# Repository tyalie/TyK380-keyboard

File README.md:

# TyK380 - A Logitech K380 based custom membrane keyboard

This project uses Logitech K380 keyboard and fully replaces its internal logic,
equipping it with cool features like the ZMK keyboard firmware, USB and an integrated
Li-Ion battery.

## The "_Whyyy_ thoo?"

This project was born out of the need for a very robust but lightweight keyboard and
my custom key layout needs. I wanted a keyboard where one doesn't need an extra
casing when it is squeezed between your laptop and books inside an already struggling
backpack without losing the comfort of key layers, macros, tap-dance and more.

The choice fell on the Logitech K380, as it is easy to source, cheap (for a custom
keyboard), has a build in on/off switch and already very robust. Additional perks are
the membrane switches, which I personally prefer over normal MK switches and are
essentially indestructible.

## The mod

The actual logic inside the original K380 is contained on a small PCB in the upper
left corner (from the top) with the key matrix attached using an FPC cable. This
makes it really easy to trash it and put your own PCB inside. The Li-Ion battery also
fits snugly in the previous AAA battery compartment.

The `hardware` folder contains the schematic and PCB for the mod-chip. It uses an
nRF52840 processor for wireless (and wired) connectivity, uses WS2812 for status LEDs
and integrates a sensible Li-Ion charging IC. Except for the newly added USB port and
a few more LED colors, the mod is essentially indistinguishable from the outside.

The only part of the mod, that requires a bit more effort besides potentially
soldering the PCB, is the drilling on the case for the USB-C port. In my first
revisions also integrated a completely oversized Li-Ion battery which didn't fit into
the battery bay without some subtractive manufacturing.

### Features

- nRF52840 - a low power, but feature-rich wireless IC
- ZMK support
- easy to integrate
- replaces AAA batteries with a Li-Ion battery
- a fully functioning USB port, for charging, connecting and programming
- RGB status LEDs

### Limitations

Besides not being able to really mix up the keyboard layout, the biggest problem
there is with the keyboard is the lack of phantom key blocking. The keyboard matrix
itself lacks any kind of diodes - presumably to save on costs - and is such prone to
ghosting. In normal use one doesn't really notice that, as the vendor firmware only
supports three key presses at a time and the key matrix traces are routed all over
the place, so that common key combinations won't result in ghost key presses.

## Contributing

Before you start editing the hardware here, you should install the [marbastlib
plugin](https://github.com/ebastler/marbastlib) into your KiCad. It contains the
footprints and 3D models for the HolyIoT board.

Otherwise, feel free to go. But if you want to contribute anything to the main
hardware, please open an issue first. I'm currently a bit unsure how collaboration
could work with KiCad projects as merging changes isn't really trivial here.

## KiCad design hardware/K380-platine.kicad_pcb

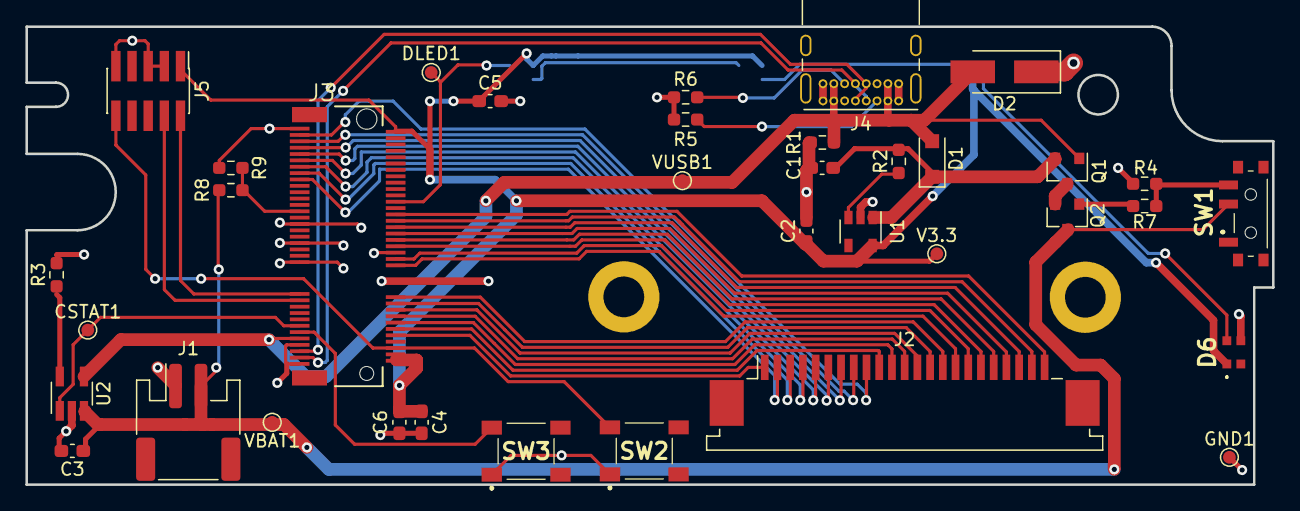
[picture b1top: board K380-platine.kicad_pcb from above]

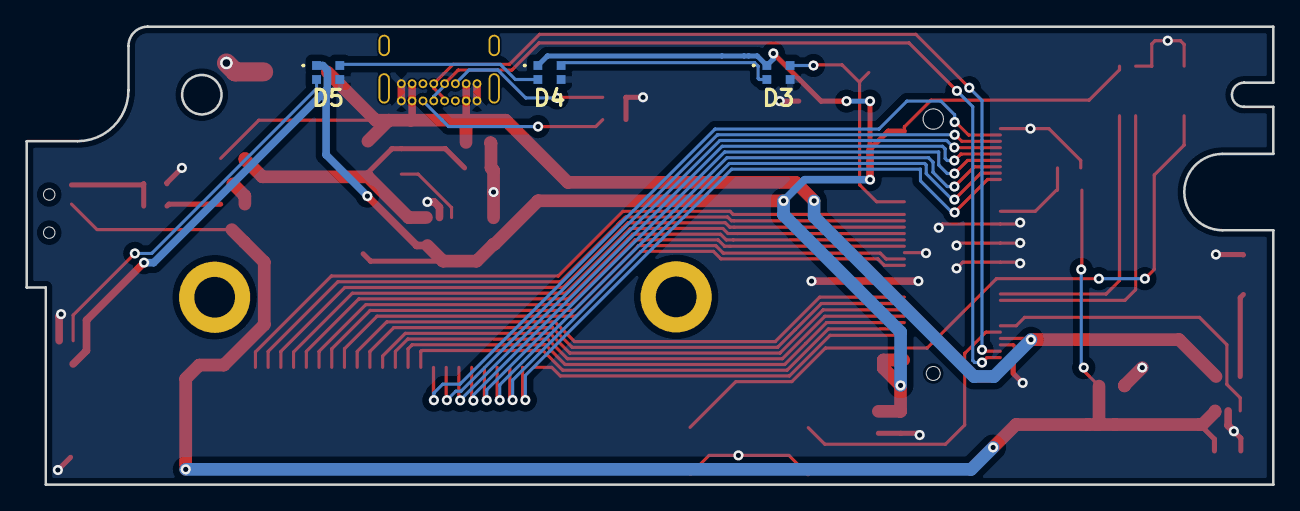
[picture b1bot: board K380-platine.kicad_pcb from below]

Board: 2 copper layers, 98.0 x 36.0 mm, 39 parts (3 on the bottom side), 48 nets.

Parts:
C1, C3, C4: 10uF; C_0603_1608Metric_Pad1.08x0.95mm_HandSolder
C2: 4.7uF; C_0603_1608Metric_Pad1.08x0.95mm_HandSolder
C5, C6: 0.1uF; C_0603_1608Metric_Pad1.08x0.95mm_HandSolder
CSTAT1: T_CSTAT; TestPoint_Pad_D1.0mm
D1: MBR1020VL; D_SOD-123F
D2: TVS 5V; D_SMA_Handsoldering
D3, D4, D5, D6: WS2812B; WS28122020
DLED1: T_DLED; TestPoint_Pad_D1.0mm
GND1: T_GND; TestPoint_Pad_D1.0mm
J1: JST-PH 2; JST_PH_S2B-PH-SM4-TB_1x02-1MP_P2.00mm_Horizontal
J2: Conn_01x23; TE_2-84952-3_1x23-1MP_P1.0mm_Horizontal
J3: MicroMod-M.2E; M.2-CONNECTOR-E
J4: USB_C_Receptacle_USB2.0; USB_C_Receptacle_GCT_USB4085
J5: Conn_ARM_JTAG_SWD_10; PinHeader_2x05_P1.27mm_Vertical_SMD
Q1: PMost Enc FET -20V; SOT-23
Q2: Q_NMOS_DGS; SOT-23
R1, R2, R8, R9: 100K; R_0603_1608Metric_Pad0.98x0.95mm_HandSolder
R3: RProg; R_0603_1608Metric_Pad0.98x0.95mm_HandSolder
R4: 100M; R_0603_1608Metric_Pad0.98x0.95mm_HandSolder
R5, R6: 5.1k 20%; R_0603_1608Metric_Pad0.98x0.95mm_HandSolder
R7: 100; R_0603_1608Metric_Pad0.98x0.95mm_HandSolder
SW1: EG1215AA
SW2, SW3: SW_Push; MJTP1140AAUTR - Fixed
U1: XC6220B331MR; SOT-23-5
U2: MCP73831-2-OT; SOT-23-5_HandSoldering
V3.3: T_V3.3; TestPoint_Pad_D1.0mm
VBAT1: T_VBAT; TestPoint_Pad_D1.0mm
VUSB1: T_VUSB; TestPoint_Pad_D1.0mm

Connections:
+3V3: C2.1, C4.1, C5.1, C6.1, D3.4 (VDD), D4.4 (VDD), D5.4 (VDD), D6.4 (VDD), J3.2 (3.3V), J3.4 (3.3V), J3.74 (3.3V), J5.1 (VTref), U1.5 (VOUT), V3.3.1
+BATT: C3.1, J1.2, Q2.3 (D), R8.1, SW1.2 (B), U2.3 (VBAT)
/SWO: J3.70 (SPI_~CS1(P1.00)), J5.6 (SWO/TDO)
BOOT: J3.11 (~BOOT), SW3.2
COL1: J2.1, J3.10 (P0.27)
COL2: J2.10, J3.12 (P0.08)
COL3: J2.11, J3.14 (P0.11)
COL4: J2.12, J3.16 (P0.15)
COL5: J2.13, J3.18 (P1.08)
COL6: J2.14, J3.20 (P1.05)
COL7: J2.15, J3.22 (P1.07)
COL8: J2.16, J3.32 (P0.06)
COL9: J2.17, J3.34 (P0.04(AIN2))
COL10: J2.18, J3.38 (P0.05(AIN3))
COL11: J2.19, J3.40 (P0.29(AIN5))
COL12: J2.20, J3.42 (P0.03(AIN1))
COL13: J2.21, J3.44 (P1.13)
COL14: J2.22, J3.46 (P1.12)
COL15: J2.23, J3.48 (P1.11)
CSTAT: CSTAT1.1, J3.13 (P1.02), U2.1 (STAT)
D+: J3.3 (USB_D+), J4.A6 (D+), J4.B6 (D+)
D-: J3.5 (USB_D-), J4.A7 (D-), J4.B7 (D-)
DLED: D3.3 (DIN), DLED1.1, J3.52 (P0.26)
GND: C1.2, C2.2, C3.2, C4.2, C5.2, C6.2, D2.1 (A1), D3.2 (VSS), D4.2 (VSS), D5.2 (VSS), D6.2 (VSS), GND1.1, J1.1, J3.1 (GND), J3.7 (GND), J3.33 (GND), J3.36 (GND), J3.39 (GND), J3.45 (GND), J3.75 (GND), J4.A1 (GND), J4.A12 (GND), J4.B1 (GND), J4.B12 (GND), J5.3 (GND), J5.5 (GND), J5.9 (GNDDetect), R1.2, R3.2, R4.2, R5.1, R6.1, R9.2, SW2.1, SW3.1, U1.2 (GND), U2.2 (VSS)
unnamed: C1.1, D1.1 (K), Q1.2 (S), R2.2, U1.1 (VIN)
unnamed: D3.1 (DOUT), D4.3 (DIN)
unnamed: D4.1 (DOUT), D5.3 (DIN)
unnamed: D5.1 (DOUT), D6.3 (DIN)
unnamed: J4.A5 (CC1), R5.2
unnamed: J4.B5 (CC2), R6.2
unnamed: Q1.3 (D), Q2.2 (S)
unnamed: Q2.1 (G), R7.1
unnamed: R4.1, R7.2, SW1.3 (C)
unnamed: R2.1, U1.3 (CE)
unnamed: R3.1, U2.5 (PROG)
RESET: J3.6 (~RESET), J5.10 (~RESET), SW2.2
ROW1: J2.2, J3.59 (P0.31(AIN7))
ROW2: J2.3, J3.61 (P0.02(AIN0))
ROW3: J2.4, J3.63 (P0.10)
ROW4: J2.5, J3.65 (P0.09)
ROW5: J2.6, J3.67 (P1.14)
ROW6: J2.7, J3.69 (P1.04)
ROW7: J2.8, J3.71 (P1.06)
ROW8: J2.9, J3.73 (P0.17)
SWDCLK: J3.21 (SWDCK), J5.4 (SWDCLK/TCK)
SWDIO: J3.23 (SWDIO), J5.2 (SWDIO/TMS)
VBUS: D1.2 (A), D2.2 (A2), J3.9 (USB_VIN), J4.A4 (VBUS), J4.A9 (VBUS), J4.B4 (VBUS), J4.B9 (VBUS), Q1.1 (G), R1.1, U2.4 (VDD), VUSB1.1
VDIV: J3.49 (P0.30(AIN6)), R8.2, R9.1

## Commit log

2022-05-26 Basic PCB outline of K380 keyboard
2022-05-26 Add few major components
    - completely unconnected
    - created schematic for M.2 sparkfun nRF52840 module
    - included SparkFun footprint library
    - position a few major components on the footprint
2022-05-27 Schem: Add Power and Charging Circuit
2022-05-28 Wired USB-C
2022-05-29 Add battery con and user switches
    - changed schematic page design
    - battery can be disabled via slider switch
    - integrated library loader
    - add user and reset switch
2022-05-29 Add status LEDs
2022-05-29 Finish schematics
    - decoupling capacitors
    - connected keyboard matrix
    - changed from user to boot pin
    - add SWD connector
    - connect MicroMod connector
2022-05-29 Assigned footprint to all components
2022-05-29 Fix footprint of USB-c connector
2022-05-29 Basic sorting of components on footprint
2022-05-29 Reordered keyboard matrix pins
    - layout traces isn't as random as before
2022-05-29 Finished basic layout
2022-05-29 Change pin of DLED and CSTAT
    - cstat was misspelled so KiCad made no connection
    - DLED is closer to where it needs to be
2022-05-29 Small layout changes to improve routing
2022-05-29 Finished routing
    - GND is zone fill in bottom
2022-05-30 Simplified tracks
    as GND got to be the bottom layer, a few tracks were able be routed
    differently, simplifying the layout and increasing the connection
    between larger sections of GND.
    Also on a few components connection to GND was given the same track
    width as the power delivering lines connected to them.
2022-05-30 Add drill mills
    - needed to reroute a few tracks for it to fit
2022-05-30 Add test probes
2022-05-30 Removed unnecessary text on silk screen
    Drill holes had Ref** on PCB
2022-05-30 Moved a few silk screen text that were unreadable
2022-07-02 Add debug-keymatrix for current config
    The keymatrix actually works as expected :D
2022-07-02 Add exclusion for bom
2022-07-02 Updated gitignore to be specific to KiCad folder
2022-07-02 Upgraded kicad
    this resulted in new JSON based the kicad_pro file
2022-08-08 Modified debug-keymatrix code
    changed printout to start at 0 not 1
2022-08-08 Add basic 3D model of PCB
2022-08-09 Ignore (temporary) dev files for 3D printing
2022-08-09 Moved pcb 2D cad design file into folder
2022-08-09 Changed depth to 36mm
    The 38mm PCB fits snuggly into the top part of the case, but doesn't
    allow the bottom shell to close correctly.
2022-08-12 3D: Flattened M.2 header
    Previous M.2 header was 4.2mm high and didn't fit into the case. Now
    switched to a 1.8mm high version and it fit's quite snuggly
2022-08-12 PCB: Updated from KiCad 5.99 to KiCad 6 file format
2022-08-12 PCB: Resized PCB to fit new size constraints
    Testing with mockups showed that a 38mm deep PCB is to large to fit into
    the K380 case. A feasible size is 36mm instead. This required the
    movement of a few components on the northern most edge, which was done
    in this commit.
    Other constraints like height aren't included yet. (see C4, C6)
2022-08-12 PCB - fix: One GND of USB wasn't connected to PCB
2022-08-12 PCB: Fix DRC warnings for PCB
    - excluded fix for C4 and C6 from this commit
2022-08-12 PCB: Fix boot / reset button footprint
    The MJTP1140AAUTR is internally differently wired than the original
    footprint pad numbers would suggest. This lead to a faulty PCB which
    needed a bit of rewiring and trace cutting effort.
2022-08-12 PCB: Moved caps out from under the M.2 module
    Due to chosing a M.2 header with a height of 1.8mm instead of 4.2mm, the
    space under the SparkFun module decreased significantly. This left no
    space for any components under the module, so they needed to be moved.
    This affected the 3.3V buffering caps C4 and C6.
2022-08-12 PCB: Fixed wrongly wired NMOS
    I've ordered a GSD mosfet, which didn't go well with the previous
    pin layout so needed to change that for further layouts.
    Also assigned previously selected footprints to the symbols in the
    schematics accordingly (e.g. smaller resistors, …)
2022-08-12 PCB: Migrated from KiCad 5 to KiCad 6 files
    deleted old and unneeded file formats and replaced them
    with their newer counterparts.
    - removed .pro and .sch files as they migrated to `.kicad_*`
    - migrated library symbols from `-cache.lib`
    - updated sch path references of `.kicad_pcb`
2022-08-12 PCB: changed via sizes
    Changed all vias to 0.8mm plated, with 0.4mm drill parameter
    Noticed that previously used via sizes are quite over dimensioned for
    the purpose they need to serve. Calculated required via sizes using
    NinjaCalc and adapted PCB accordingly.
2022-08-12 CAD: modified upper right hole size to r=1.55mm
    The pin on the case is almost exactly 3mm thick, resulting in a very
    tight fit in the resulting PCB, 3D print, … This hole though doesn't
    need to be so tight fitting, that is why I increased the radius
2022-08-13 Exported gerber files
2022-08-13 Changed height of M.2 to 2.45mm
    The 1.8mm heigh M.2 E header would put the module flat on the PCB and
    has a different footprint than headers that are higher. The former isn't
    feasible as the SparkFun module has a flash storage on the bottom.
    Additionally the different footprint isn't publicly available right now
    and would need to be modeled on my own.
2022-08-13 Changed M.2 header height to 2.75mm
    the 2.45mm doesn't really exist on the market
2023-06-23 not sure what changed
    something something the M.2 connector
2023-07-02 keyboard: power: Fixed on/off switch behavior
    changes:
    - fix on/off switch behavior
    - move away from global labels for power symbols
    - add SWO trace to Cortex-M debug connector
    The on/off switch is a SPDT switch which has two possible
    configurations. Use the one where I don't need to invert the signal as
2023-07-02 keyboard: Upgraded to newest KiCad version
2023-07-02 firmware: Added my K380 zmk fork as submodule
    Is now in folder zmk-firmware
2023-07-02 reorder: moved old stuff into folder debug-tools
    Things like the 3D model and my debug-keymatrix minimal project, which
    helped me figure out the dimensions and the internal wiring, are not
    needed anymore. In turn they have now been moved into a folder called
    `debug-tools`.
2023-07-02 refactor: rename schematics folder into hardware
    Had previously the non-descriptive name "K380-platine" for the folder
    which contained all schematics. It's now named into "hardware" (for now)
2023-07-02 add license: CERN OHL version 2
    The CERN OHL seems to be a standard license in the field of open
    hardware projects. Reading through it doesn't seem too bad, so here we
    go.
    (Do I now get extra nerdy points?)
2023-07-02 firmware: Set submodule to track correct branch
2023-07-02 project: Added README for new users
2023-07-03 hardware: update KiCad and fix library issue
    - opened all files in newest KiCad version (7.0.5) and let it update
    - fixed library Symbol for EG1215AA switch
    - design of through holes threw "Invalid zero sized pads" error
    - fixed according to this post:
    - https://forum.kicad.info/t/invalid-zero-sized-pad-pinned-to-1-m-in-file-error-in-footprint-file/40908/4
2023-07-03 hardware: update WS2812B 2020 symbol [unrooted]
    Previously the footprint and symbol pinout didn't match the WS2812B 2020
    datasheet. I previously thought that I could get away with just using
    the WS2812B symbol, but in my blissful ignorance I didn't notice that
    the WS2812B symbol has a different ordering of the number pins.
    This patch introduces a new WS2812B_2020 symbol in LibraryLoader, which
    is a copy of the WS2812B symbol, but with the pinout from the datasheet.
2023-07-03 hardware: schematic: Moved MCU to separate page
    With this separation of content, it will make the future change of
    directly placing the nRF52840 module onto the board much easier, as all
    parts that replace the micromod module will be part of this new sheet.
2023-07-03 Update README.md
    change spelling
2023-07-05 hardware: completed rev 0.2α (pre-verify)
    This is a bigger change from the iteration. The MicroMod has been
    replaced with an HolyIoT nRF52840, which can be directly soldered onto
    the board. This guarantees minimal space usage, while reducing the
    complexity to implement an MCU on our own.
    Additionally this iteration moves away from reserving a gpio port per
    keyboard matrix trace, and instead makes use of an GPIO shift register
2023-07-05 Revert "hardware: first nRF52840 raw tries"
    Wanna start from a clean slate. See referenced commit on why I'm doing
    this.
    This reverts commit 5420c1d1e1bdfd9146d776c48bdd16e2d166426d.
2023-07-05 hardware: first nRF52840 raw tries
    The current schematic should (in theory) be a complete setup for the
    nRF52840 chip with power and everything.
    In the footprint first routing attempts have been made, but this has
    been without real success for now, especially as the nRF52840 is a hell
    of a chip to implement. Ignoring the whole "need to do own RF" here,
    it's almost impossible to get the inner pins out from under the chip
2023-07-05 readme: Added contributing segment
    Added reference to the marbastlib project for the HolyIoT footprints and
    added a statement that changes should be discussed beforehand as I don't
    know yet how to do collaboration with KiCad projects.
